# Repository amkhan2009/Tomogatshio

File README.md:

Designed and made a simple looking tomagatshi that will use keyboard switches to be able to make it play. It will include some nice looking parts and pieces such as a buzzer and some other things along those lines.

It will use a Oled screen and 3 cutom inputs to be able to make it play and will incldue some nice looking lilies on the side of the circuit to make it look more appealing.

| # | Item | Description | Qty | Unit (USD) | Import (USD) | Ship (USD) | Line Total (USD) | Supplier | Notes |
|---|------|-------------|-----|-----------|-------------|-----------|-----------------|----------|-------|
| 1 | PBT Keycap DSA 1U Blank | DSA 1U keycap, not engraved | 1 | $2.87 | $0.32 | $0.00 | $3.19 | SZElectronic Store | Only 6 left; AliExpress |
| 2 | OLED Display 0.96in 128×64 | SSD1306, I2C/SPI, 4-pin, yellow/blue | 1 | $3.83 | $0.47 | $0.00 | $4.30 | Shop1104933341 Store | Only 10 left; AliExpress |
| 3 | Tactile Switch Holy Panda | 3-pin, 55g/62g/67g POM | 1 | $4.38 | $0.49 | $0.00 | $4.87 | Powerpuff Girls Switch Store | Only 2 left; AliExpress |
| 4 | Active Buzzer Ultra Thin | 12065 12mm×6.5mm, 3V/5V/12V magnetic | 1 | $1.54 | $0.17 | $3.04 | $4.75 | CanHuiSheng Store | 10 pcs listing |
| 5 | Female Pin Header Socket | 2.54mm, straight, double row, 2–40P | 1 | $0.75 | $0.08 | $5.87 | $6.70 | DQLZV Official Store | — |
| 6 | LiPo Battery 3.7V 2000mAh | 103450, JST 1.25mm 2-pin | 1 | $8.41 | $0.95 | $5.53 | $14.89 | EHAO Lipo Battery Store | 3 pcs listing |
| 7 | ESP32-C3 Dev Board | Seeed XIAO ESP32C3, WiFi/BLE, 4MB | 1 | $5.64 | $0.63 | $5.71 | $11.98 | Your Cee Store | 10 pcs listing available |
| 8 | Custom PCB | — | 1 | $7.00 | $2.00 | $3.00 | $7.00 | — | — |
| **Total** | | | | **$34.42** | **$5.11** | **$23.15** | **$57.68** | | |

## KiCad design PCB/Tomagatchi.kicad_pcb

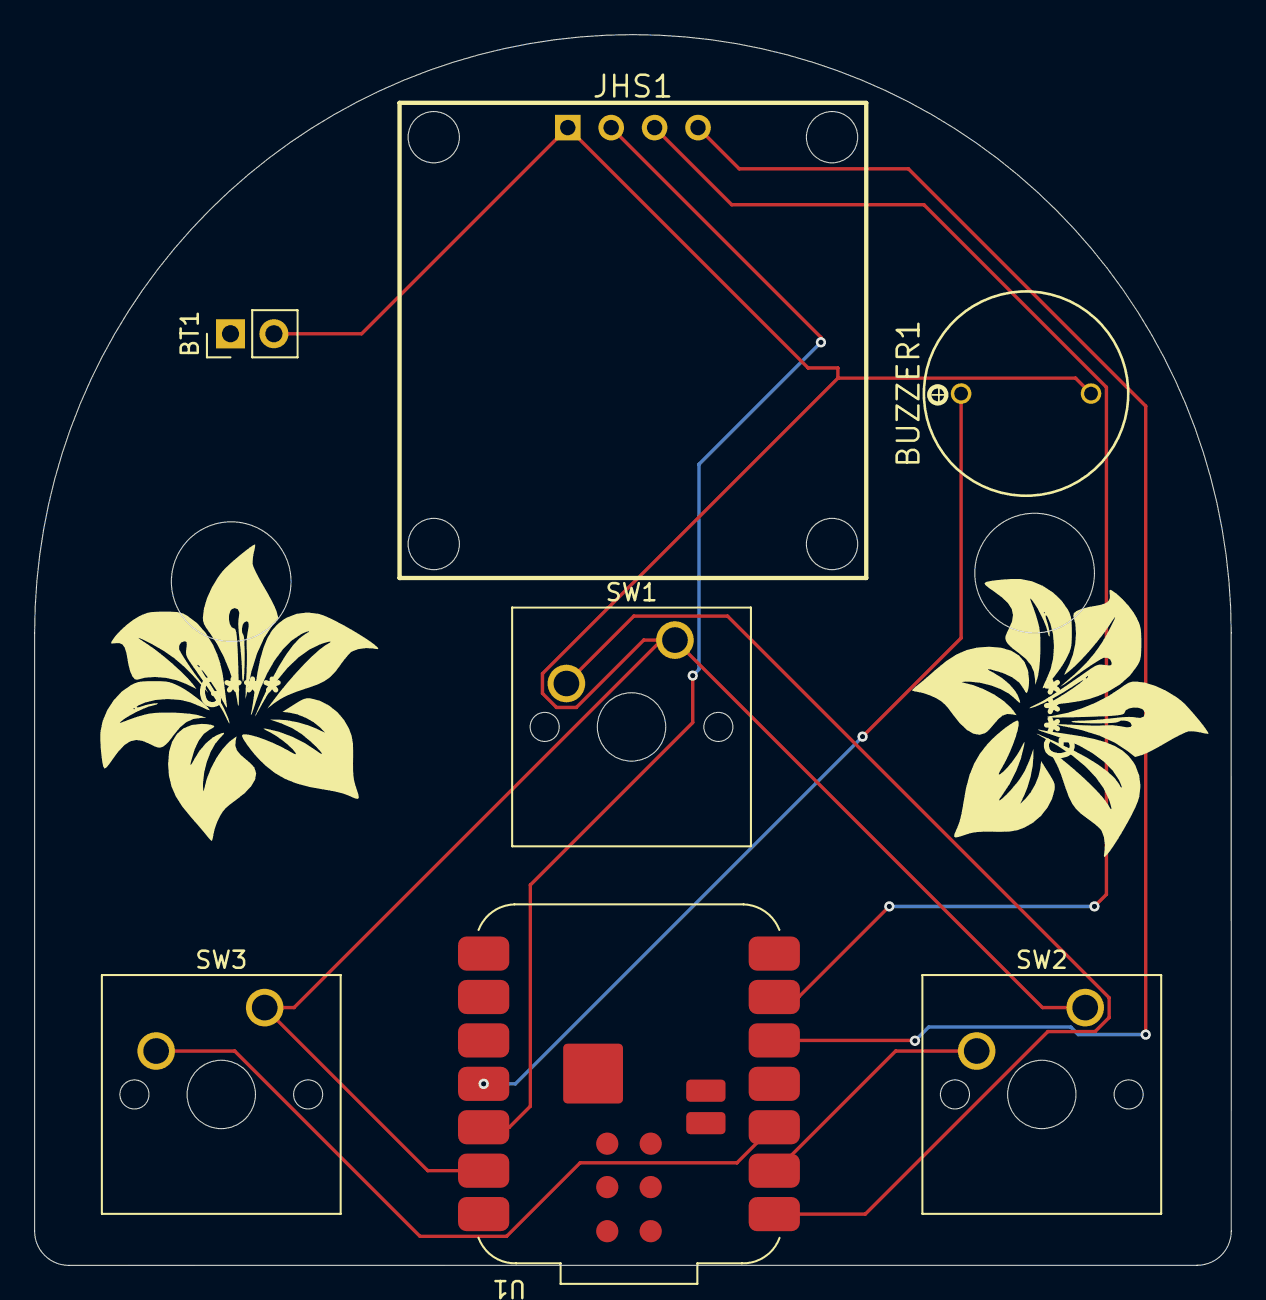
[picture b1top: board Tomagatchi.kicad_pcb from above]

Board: 2 copper layers, 70.0 x 72.0 mm, 7 parts (0 on the bottom side), 8 nets.

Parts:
BT1: Battery_Cell; PinHeader_1x02_P2.54mm_Vertical
BUZZER1: 1207-P6.5MM; BUZ-TH_BD11.8-P7.60_XHXDZ-TMB12065
JHS1: HS96L03W2C03; OLED-TH_HS96L03W2C03
SW1, SW2, SW3: SW_Push; SW_Cherry_MX_1.00u_PCB
U1: XIAO-ESP32-C3-SMD; MCU_Seeed_ESP32C3

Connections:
+3V3: JHS1.2, U1.12 (3V3)
GND: BT1.2 (-), BUZZER1.2, JHS1.1, SW1.1, SW2.1, SW3.1, U1.13 (GND)
unnamed: BUZZER1.1, U1.11 (GPIO10_D10_MOSI)
unnamed: JHS1.3, U1.6 (GPIO7_D5_SCL)
unnamed: JHS1.4, U1.5 (GPIO6_D4_SDA)
unnamed: SW1.2, U1.1 (GPIO2_A0_D0)
unnamed: SW2.2, U1.2 (GPIO3_A1_D1)
unnamed: SW3.2, U1.3 (GPIO4_A2_D2)

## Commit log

2026-05-04 Add additional images to README
2026-05-04 Rename Tomo.zip to Gerber.zip
2026-05-04 Rename Screenshot 2026-05-03 205320.png to 3d View of the PCB
2026-05-04 Rename BOM (1).csv to BOM.csv
2026-05-14 Create Pro
